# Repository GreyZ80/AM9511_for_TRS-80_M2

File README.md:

# AM9511_for_TRS-80_M2
Design of a PCB board (started Jul 13, 2025) that enables the use of a AM9511 Arithmetic Processing Unit (APU) on a TRS-80 Model II.\
The AM9511 was developed by AMD. Intel licensed it and created the Intel 8231.\
The chips are not difficult to obtain (search iainventory.com or AliExpress.com for AM9511). So far I have not yet found fake chips 😃.

A small proto board was developed for the TRS-80 Model II. The design is based on the sample circuits in the AM9511 documentation, with modifications needed to use it in a TRS-80 Model II. Check the AM9511A Processor Manual for details. 
The ZIF socket pictured was used for easy swapping of AM9511 for chip testing. A final board would use a standard socket.

## Specifications

Specifications of the board:
- I/O mapped on addresses 064h (100 decimal) and 065h (101 decimal). This can be changed by reprogramming the GAL chip. Note that ports 0C0h and higher are in use by the internal and peripheral hardware .
  - 064h  reading and writing of data
  - 065h  reading status and writing of commands
- Port address decoding and RD*, WR*, CS* and RESET* signal generation is done using a GAL 22V10. The .PLD file used for the compilation in WinCupl has been added. The .JED file can be used by a GAL programmer.
- Running on 3MHz with the option to connect an external clock signal.
- D0~D7 of the TRS-80 Model II bus are inverted on the bus. A 74LS640 takes care the conversion. This is an Octal <ins>Inverting</ins> Bus Transceiver (Tri-State)
- Jumpers are used for configuring the PAUSE* and END* signals.
- Testpoints are present for checking of the signals on the board.
- The board provides both +5V and +12V to the AM9511.

## Schematic

The schematic provides jumpers enabling various modes of operation.
- JP1 is only used for clock generators that have an Enable line. Otherwise it can be left open.
- JP2 is set when running in interrupt mode. The AM9511 will trigger an interrupt when ready. Leave open when using polling (reading the Busy bit).
- Set JP3 to connect the on-board clock to the AM9511.
- Set jP4 to use the AM9511 Pause* to activate Z80 Wait*.

A data buffer interfaces the AM9511 to the TRS-80 databus. A GAL chip takes care of address decoding and signal inversion for RESET is performed by a 22V10 GAL chip.

## Board design

The board was designed using [Kicad](https://www.kicad.org/) version 6.0 and [Freerouting](https://github.com/freerouting/freerouting/) running on my ASUS Chromebook.\

## Usage

>[!CAUTION]
> **Do not touch the AM9511 APU during use, as it becomes really hot. Consider placing a heatsick on the chip.**

First use of the board is in I/O mode. This means that status is polled on port 065h. Write timing is influenced by the AM9511 by means of the PAUSE* signal when it is connected to the Z80 WAIT* line. For testing this is not needed and the Busy flag can be monitored at Port 065h.\
A first check for operation/presence of the AM9511 can be done by repeatedly reading from port 064h. A read from the stack not only puts the byte that is on top of the stack in register A, but also places the byte from the top of the stack at the bottom of the stack. Actually the stack pointer is moved. The stack is 16 bytes deep.
This means that after reading 16 bytes, the data read from the stack is repeated. I have seen that after a reset most, but not all, bytes are set to 0FFh.

The following Z80 assembler code performs a simple 16 bit addition.

```ruby
LD    C, 064H    ; data port  
LD    A, 34H     ; LSB of the 16 bit value 01234H  
OUT   (C),A  
LD    A, 12H     ; MSB
OUT   (C),A  
LD    A, 78H     ; LSB of the 16 bit value 05678H  
OUT   (C),A  
LD    A, 56H     ; MSB
OUT   (C),A  
LD    C,065H     ; command port  
LD    A, 06CH    ; Instruction to add 2 16 bit numbers  
LD    C,064H     ; data port  
IN    A,(C)      ; get MSB of the result (should be 068H)  
IN    A,(C)      ; get LSB of the result (should be 0ACH)  
```

Of course the same can be achieved using Basic. Just boot your machine and type Basic at the prompt.
```
100 rem ---- AM9511 ----
110 DP = &H64  :REM DATA PORT (64h)
120 CP = &H65  :REM Command/Status port (65h)
130 A = &H1234
140 B = &H5678
150 MSB = INT(A/256)
160 LSB = MOD(A,256)
170 OUT DP,LSB : OUT DP, MSB
180 MSB = INT(B/256)
190 LSB = MOD(B,256)
200 OUT DP,LSB : OUT DP, MSB
210 OUT CP,&H6C  :REM 06CH is the value of the instruction to add 2 16 bit numbers 
220 MSB = INP(DP) : LSB = INP(DP)
230 R = MSB * 256 + LSB
240 PRINT A;" +";B;" =";R

```

See [barberd/coco9511pak](https://github.com/barberd/coco9511pak) for support of the AM9511 on the Tandy Color Computer.

**Source and License**
-------------------------------------
The design is copyright 2024, 2026 by Ruud Broers. The design is open source, distributed via the GNU GPL version 3 license. Please see the LICENSE file for details.

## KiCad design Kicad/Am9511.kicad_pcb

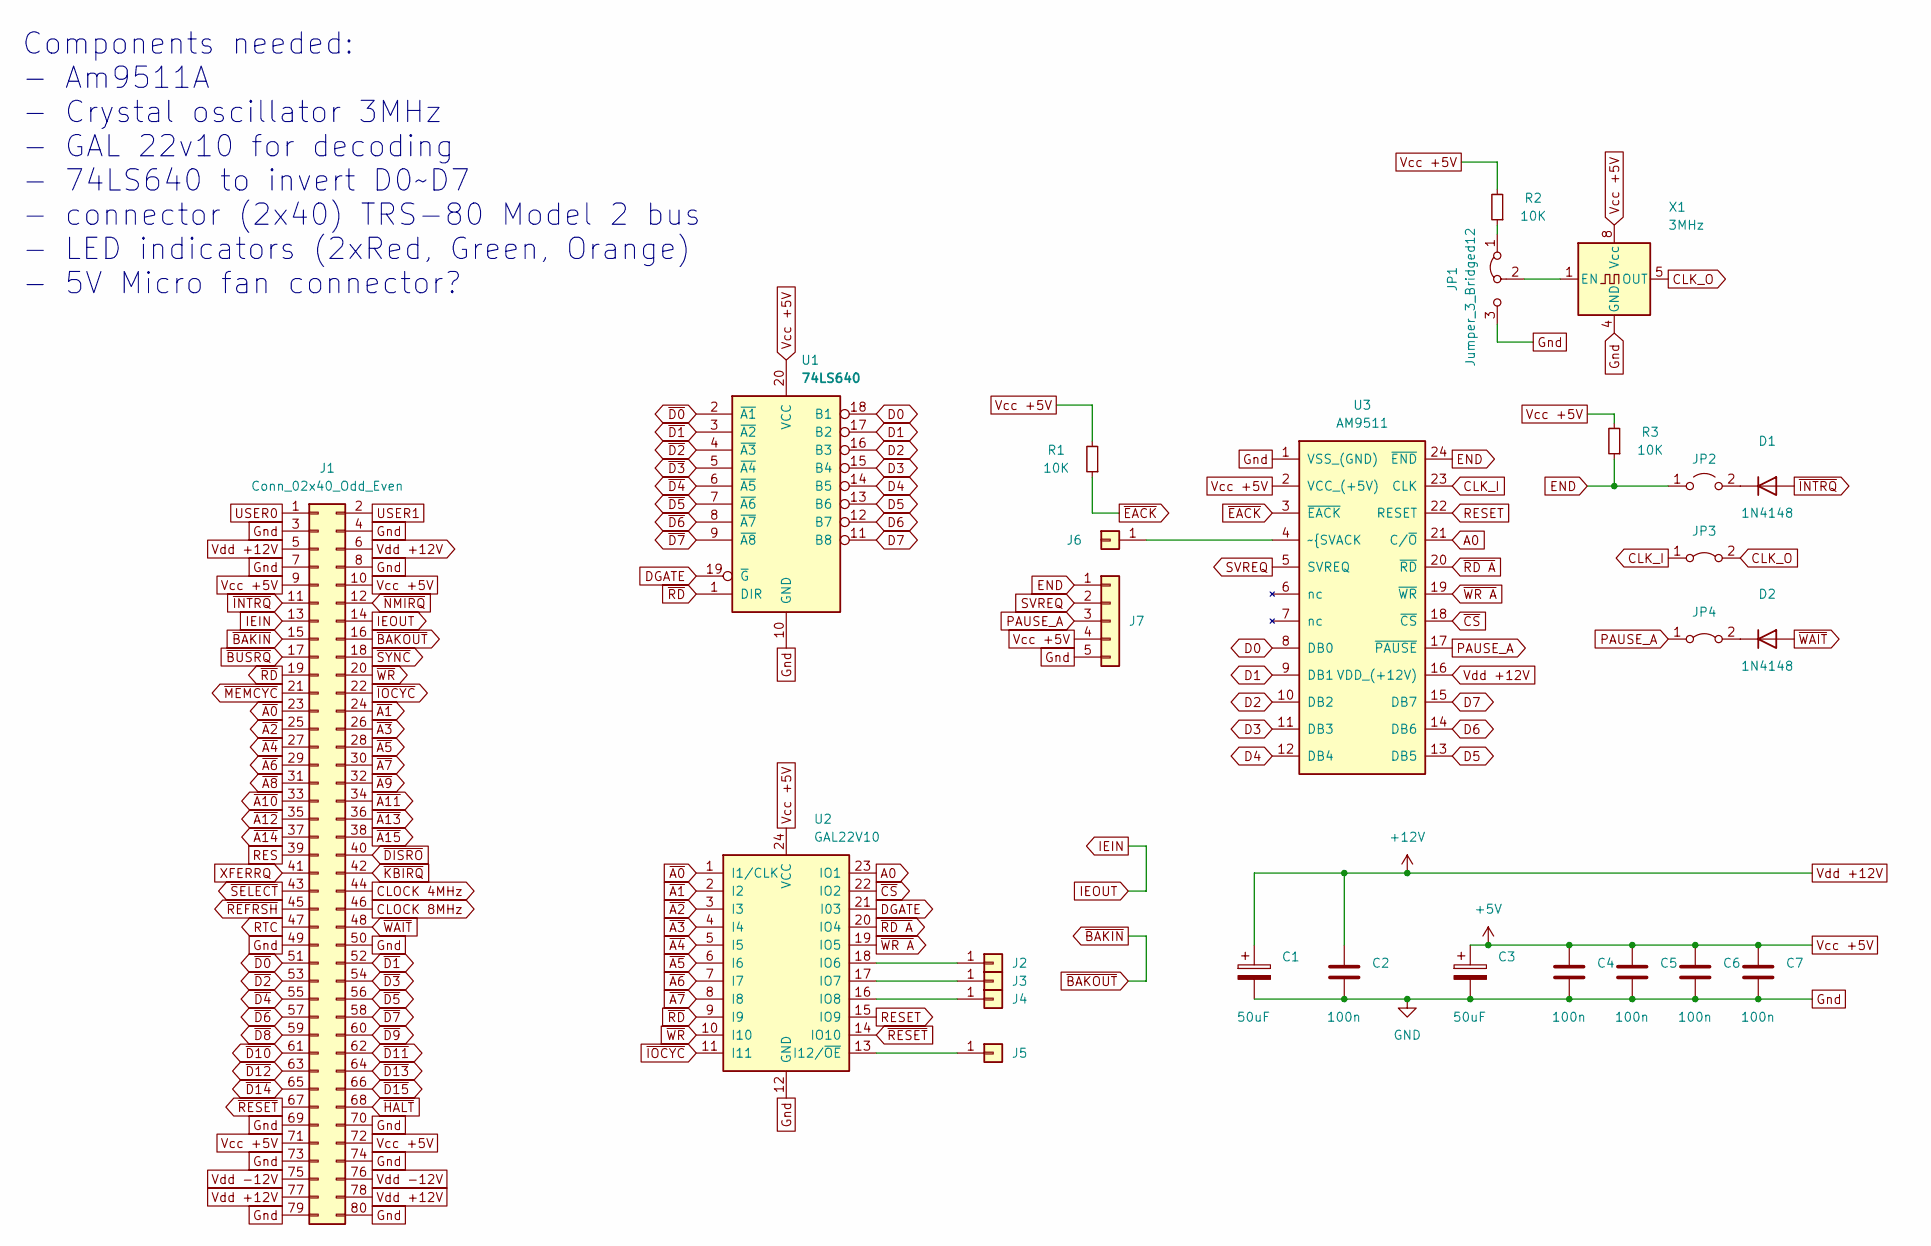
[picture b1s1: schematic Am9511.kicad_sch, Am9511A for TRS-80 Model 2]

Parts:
C1, C3: 50uF; CP_Radial_D6.3mm_P2.50mm
C2, C4, C5, C6, C7: 100n; C_Disc_D3.0mm_W2.0mm_P2.50mm
D1, D2: 1N4148; D_DO-35_SOD27_P7.62mm_Horizontal
J1: Conn_02x40_Odd_Even; BUS_TANDY80_M
J2, J3, J4, J5, J6: Conn_01x01; PinHeader_1x01_P2.54mm_Vertical
J7: Conn_01x05; PinHeader_1x05_P2.54mm_Vertical
JP1: Jumper_3_Bridged12; PinHeader_1x03_P2.54mm_Vertical
JP2: Jumper_2_Open; PinHeader_1x02_P2.54mm_Vertical
JP3, JP4: Jumper_2_Bridged; PinHeader_1x02_P2.54mm_Vertical
R1, R2, R3: 10K; R_Axial_DIN0207_L6.3mm_D2.5mm_P15.24mm_Horizontal
U1: 74LS640; DIP-20_W7.62mm_Socket
U2: GAL22V10; DIP-24_W7.62mm_Socket
U3: AM9511; DIP-24_W15.24mm_Socket
X1: 3MHz; Oscillator_DIP-8

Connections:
A0: U2.23 (IO1), U3.21 (C/~O)
CLK_I: JP3.1 (A), U3.23 (CLK)
CLK_O: JP3.2 (B), X1.5 (OUT)
CLOCK 4MHz: J1.44
CLOCK 8MHz: J1.46
D0: U1.18 (B1), U3.8 (DB0)
D1: U1.17 (B2), U3.9 (DB1)
D2: U1.16 (B3), U3.10 (DB2)
D3: U1.15 (B4), U3.11 (DB3)
D4: U1.14 (B5), U3.12 (DB4)
D5: U1.13 (B6), U3.13 (DB5)
D6: U1.12 (B7), U3.14 (DB6)
D7: U1.11 (B8), U3.15 (DB7)
DGATE: U1.19 (~G), U2.21 (I03)
END: J7.1, JP2.1 (A), R3.1, U3.24 (~END)
Gnd: C1.2, C2.2, C3.2, C4.2, C5.2, C6.2, C7.2, J1.3, J1.4, J1.7, J1.8, J1.49, J1.50, J1.69, J1.70, J1.73, J1.74, J1.79, J1.80, J7.5, JP1.3 (B), U1.10 (GND), U2.12 (GND), U3.1 (VSS_(GND)), X1.4 (GND)
IEIN: J1.13, J1.14
unnamed: D1.1 (K), JP2.2 (B)
unnamed: D2.1 (K), JP4.2 (B)
unnamed: J2.1, U2.18 (IO6)
unnamed: J3.1, U2.17 (IO7)
unnamed: J4.1, U2.16 (IO8)
unnamed: J5.1, U2.13 (I12/~OE)
unnamed: J6.1, U3.4 (~{SVACK)
unnamed: JP1.1 (A), R2.1
unnamed: JP1.2 (C), X1.1 (EN)
PAUSE_A: J7.3, JP4.1 (A), U3.17 (~PAUSE)
RES: J1.39
RESET: U2.15 (IO9), U3.22 (RESET)
RTC: J1.47
SVREQ: J7.2, U3.5 (SVREQ)
USER0: J1.1
USER1: J1.2
Vcc +5V: C3.1, C4.1, C5.1, C6.1, C7.1, J1.9, J1.10, J1.71, J1.72, J7.4, R1.2, R2.2, R3.2, U1.20 (VCC), U2.24 (VCC), U3.2 (VCC_(+5V)), X1.8 (Vcc)
Vdd +12V: C1.1, C2.1, J1.5, J1.6, J1.77, J1.78, U3.16 (VDD_(+12V))
Vdd -12V: J1.75, J1.76
XFERRQ: J1.41
~A0: J1.23, U2.1 (I1/CLK)
~A1: J1.24, U2.2 (I2)
~A2: J1.25, U2.3 (I3)
~A3: J1.26, U2.4 (I4)
~A4: J1.27, U2.5 (I5)
~A5: J1.28, U2.6 (I6)
~A6: J1.29, U2.7 (I7)
~A7: J1.30, U2.8 (I8)
~A8: J1.31
~A9: J1.32
~A10: J1.33
~A11: J1.34
~A12: J1.35
~A13: J1.36
~A14: J1.37
~A15: J1.38
~BAKIN: J1.15, J1.16
~BUSRQ: J1.17
~CS: U2.22 (IO2), U3.18 (~CS)
~D0: J1.51, U1.2 (~A1)
~D1: J1.52, U1.3 (~A2)
~D2: J1.53, U1.4 (~A3)
~D3: J1.54, U1.5 (~A4)
~D4: J1.55, U1.6 (~A5)
~D5: J1.56, U1.7 (~A6)
~D6: J1.57, U1.8 (~A7)
~D7: J1.58, U1.9 (~A8)
~D8: J1.59
~D9: J1.60
~D10: J1.61
~D11: J1.62
~D12: J1.63
~D13: J1.64
~D14: J1.65
~D15: J1.66
~DISRO: J1.40
~EACK: R1.1, U3.3 (~EACK)
~HALT: J1.68
~INTRQ: D1.2 (A), J1.11
~IOCYC: J1.22, U2.11 (I11)
~KBIRQ: J1.42
~MEMCYC: J1.21
~NMIRQ: J1.12
~RD A: U2.20 (IO4), U3.20 (~RD)
~RD: J1.19, U1.1 (DIR), U2.9 (I9)
~REFRSH: J1.45
~RESET: J1.67, U2.14 (IO10)
~SELECT: J1.43
~SYNC: J1.18
~WAIT: D2.2 (A), J1.48
~WR A: U2.19 (IO5), U3.19 (~WR)
~WR: J1.20, U2.10 (I10)

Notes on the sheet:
Components needed: - Am9511A - Crystal oscillator 3MHz - GAL 22v10 for decoding - 74LS640 to invert D0~D7 - connector (2x40) TRS-80 Model 2 bus - LED indicators (2xRed, Green, Orange) - 5V Micro fan connector?

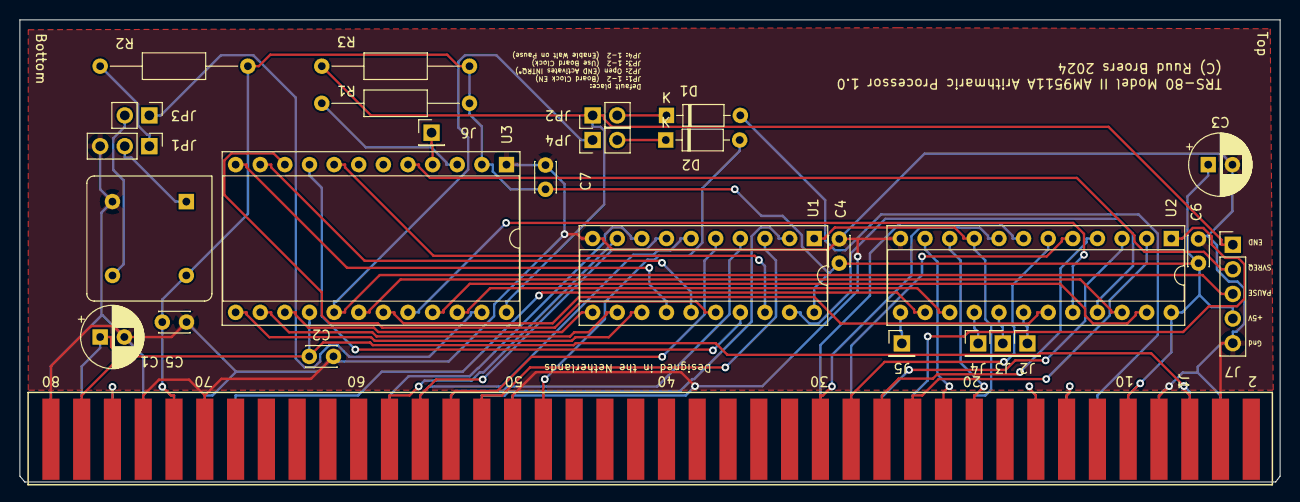
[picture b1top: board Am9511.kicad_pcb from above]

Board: 2 copper layers, 130.0 x 47.7 mm, 27 parts (0 on the bottom side), 57 nets.

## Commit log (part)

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2025-07-13 Update README.md
    Initial version
2025-08-02 Add files via upload
    Files used for the prototype PCB
2025-08-29 Added schematic
